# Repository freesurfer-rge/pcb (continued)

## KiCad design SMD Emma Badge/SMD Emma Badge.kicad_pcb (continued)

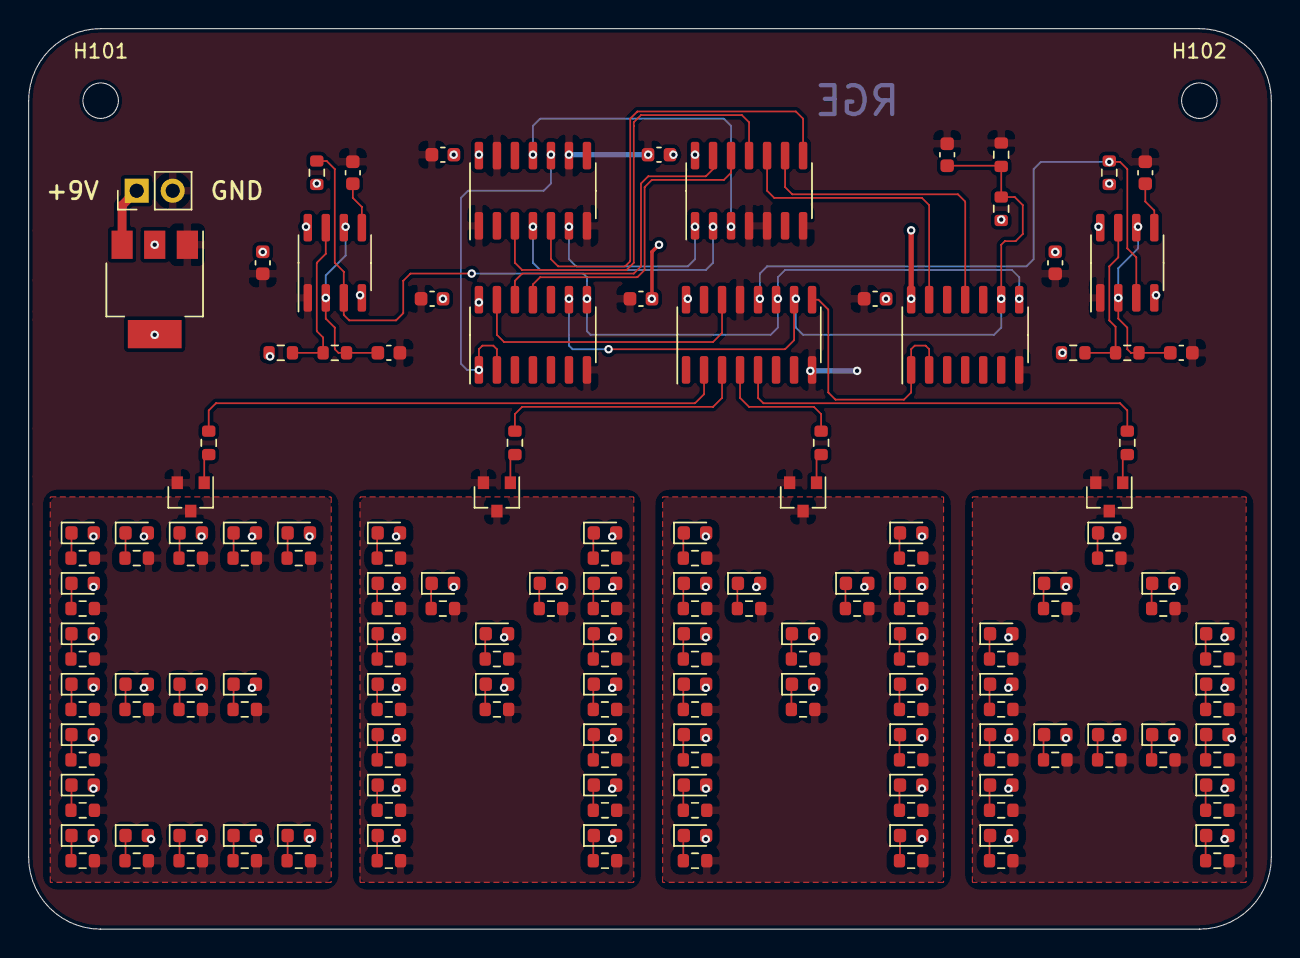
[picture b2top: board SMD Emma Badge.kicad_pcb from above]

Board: 2 copper layers, 87.6 x 63.5 mm, 179 parts (0 on the bottom side), 106 nets.

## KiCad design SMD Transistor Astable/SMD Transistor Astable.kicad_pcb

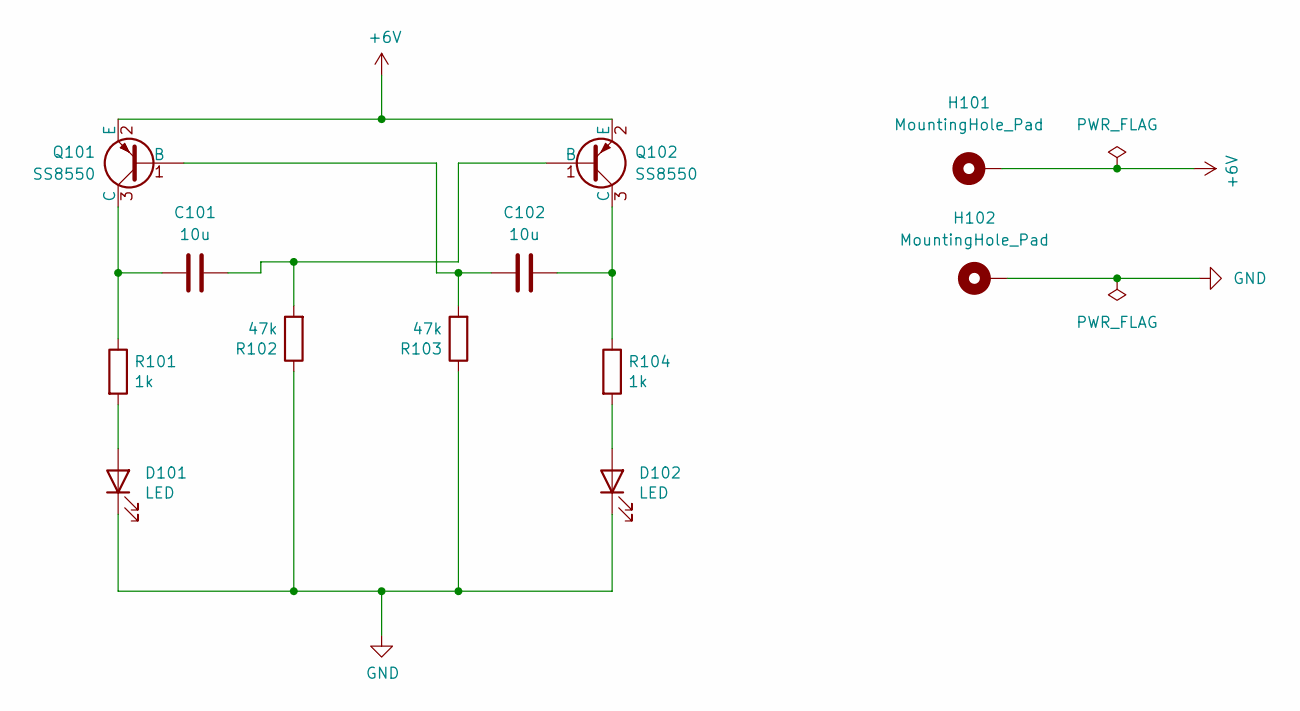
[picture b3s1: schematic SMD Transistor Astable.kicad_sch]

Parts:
C101, C102: 10u; C_0603_1608Metric; LCSC C19702
D101, D102: LED; LED_0603_1608Metric; LCSC C72043
H101, H102: MountingHole_Pad; TestPoint_Pad_2.0x2.0mm
Q101, Q102: SS8550; SOT-23; LCSC C8542
R101, R104: 1k; R_0603_1608Metric; LCSC C21190
R102, R103: 47k; R_0603_1608Metric; LCSC C25819

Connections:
+6V: H101.1, Q101.2 (E), Q102.2 (E)
GND: D101.1 (K), D102.1 (K), H102.1, R102.1, R103.1
unnamed: C101.1, Q101.3 (C), R101.1
unnamed: C101.2, Q102.1 (B), R102.2
unnamed: C102.1, Q101.1 (B), R103.2
unnamed: C102.2, Q102.3 (C), R104.1
unnamed: D101.2 (A), R101.2
unnamed: D102.2 (A), R104.2

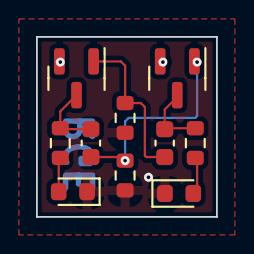
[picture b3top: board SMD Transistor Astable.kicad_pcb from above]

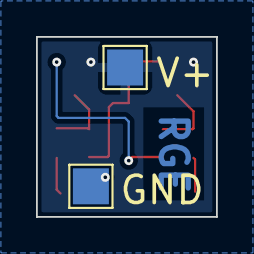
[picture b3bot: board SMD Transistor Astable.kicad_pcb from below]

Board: 2 copper layers, 10.0 x 10.0 mm, 12 parts (2 on the bottom side), 8 nets.

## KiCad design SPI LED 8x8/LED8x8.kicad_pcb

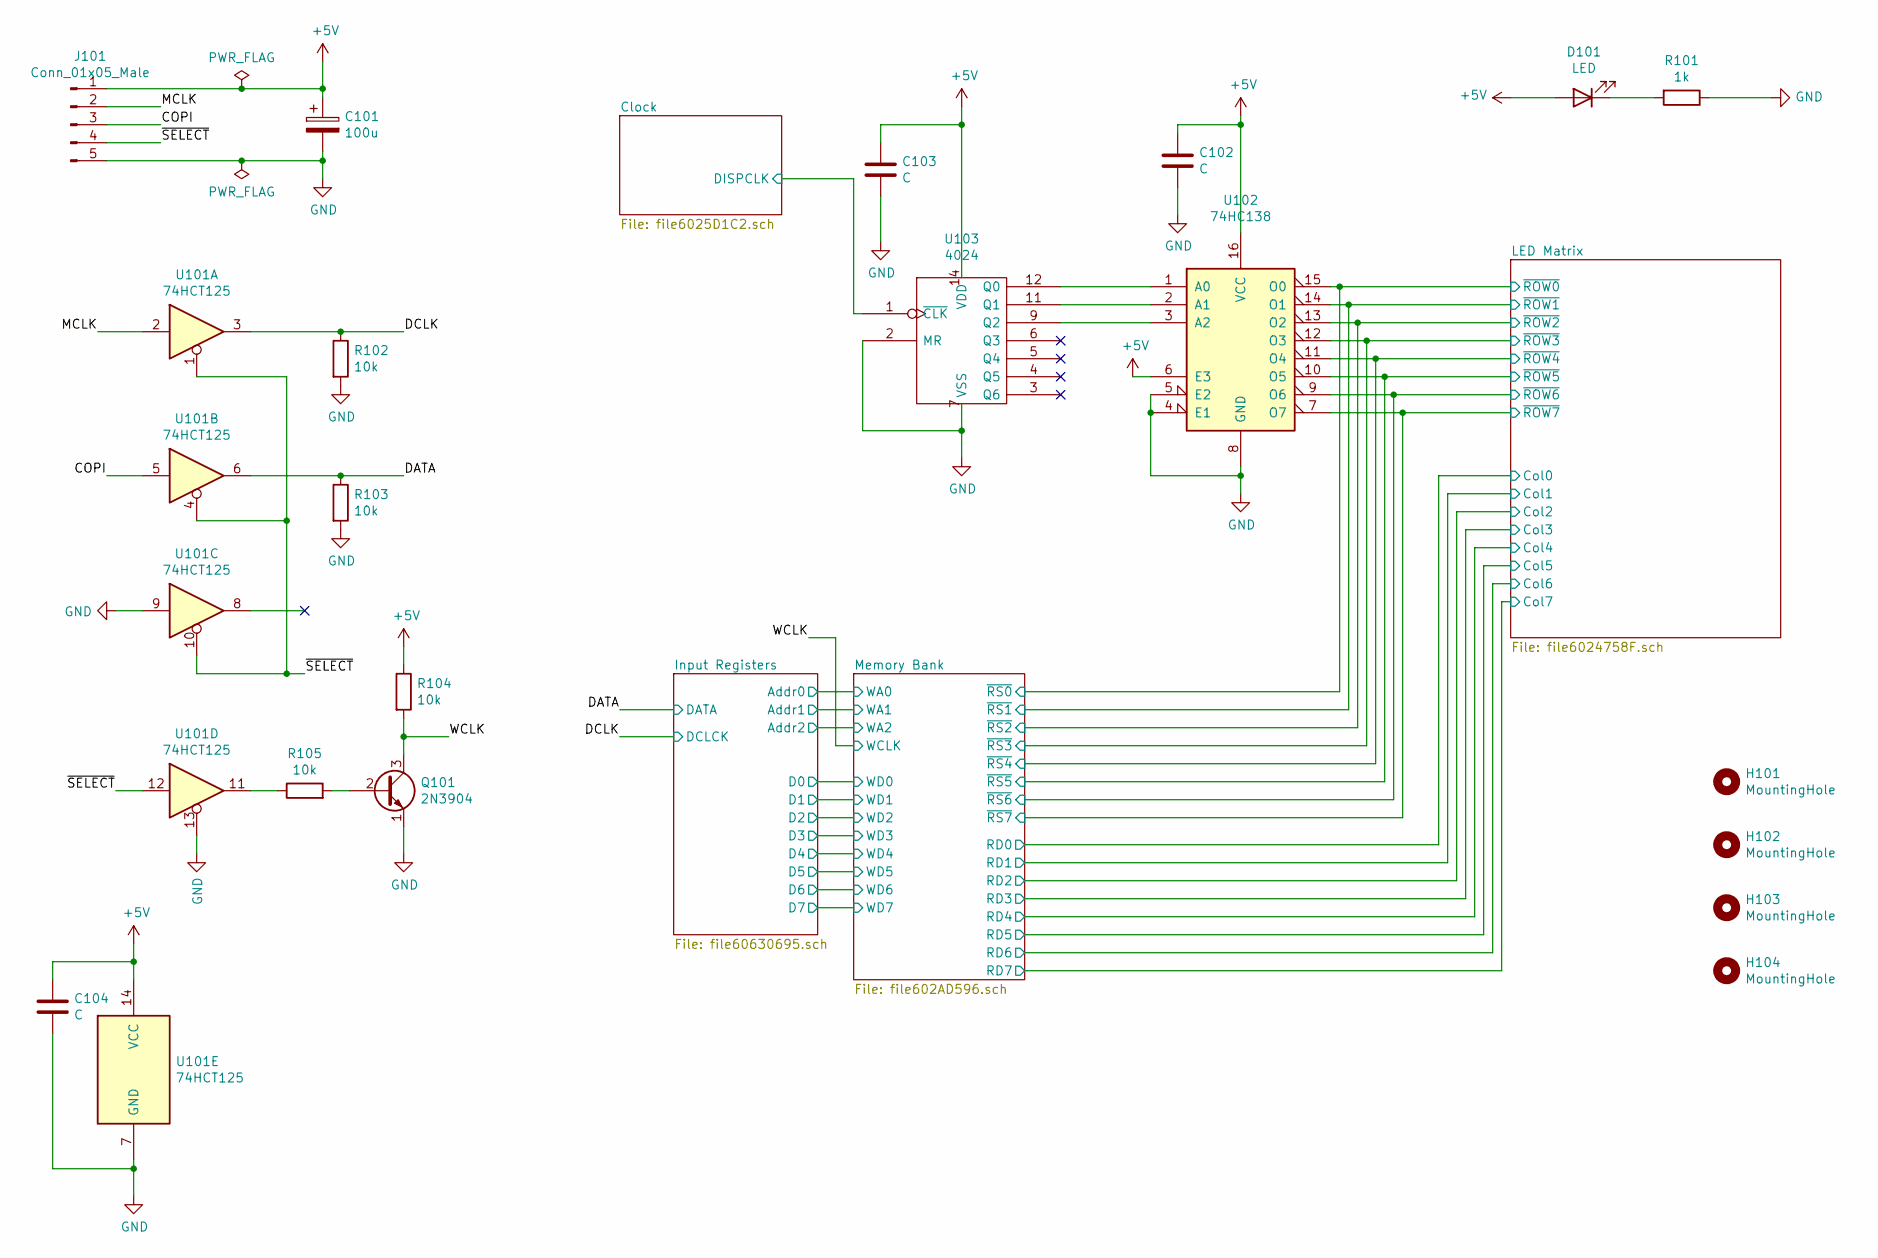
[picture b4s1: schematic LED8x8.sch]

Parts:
C101: 100u; CP_Radial_D5.0mm_P2.50mm
C102: C; C_Disc_D4.3mm_W1.9mm_P5.00mm
C103, C104: C; C_Disc_D4.7mm_W2.5mm_P5.00mm
D101: LED; LED_D5.0mm
H101, H102, H103, H104: MountingHole; MountingHole_2.7mm_M2.5
J101: Conn_01x05_Male; PinHeader_1x05_P2.54mm_Vertical
Q101: 2N3904; TO-92_Wide
R101: 1k; R_Axial_DIN0207_L6.3mm_D2.5mm_P7.62mm_Horizontal
R102, R103, R104, R105: 10k; R_Axial_DIN0207_L6.3mm_D2.5mm_P7.62mm_Horizontal
U101: 74HCT125; DIP-14_W7.62mm_Socket
U102: 74HC138; DIP-16_W7.62mm_Socket
U103: 4024; DIP-14_W7.62mm_Socket

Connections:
+5V: C101.1, C102.2, C103.2, C104.2, D101.2 (A), J101.1, R104.1, U101.14 (VCC), U102.6 (E3), U102.16 (VCC), U103.14 (VDD); also elsewhere on the board
/COPI: J101.3, U101.5
/Clock/DISPCLK: U103.1 (~CLK); also elsewhere on the board
/DATA: R103.1, U101.6; also elsewhere on the board
/DCLK: R102.1, U101.3; also elsewhere on the board
/LED Matrix/~ROW0: U102.15 (O0); also elsewhere on the board
/LED Matrix/~ROW1: U102.14 (O1); also elsewhere on the board
/LED Matrix/~ROW2: U102.13 (O2); also elsewhere on the board
/LED Matrix/~ROW3: U102.12 (O3); also elsewhere on the board
/LED Matrix/~ROW4: U102.11 (O4); also elsewhere on the board
/LED Matrix/~ROW5: U102.10 (O5); also elsewhere on the board
/LED Matrix/~ROW6: U102.9 (O6); also elsewhere on the board
/LED Matrix/~ROW7: U102.7 (O7); also elsewhere on the board
/MCLK: J101.2, U101.2
/WCLK: Q101.3 (C), R104.2; also elsewhere on the board
/~SELECT: J101.4, U101.1, U101.4, U101.10, U101.12
GND: C101.2, C102.1, C103.1, C104.1, J101.5, Q101.1 (E), R101.1, R102.2, R103.2, U101.7 (GND), U101.9, U101.13, U102.4 (E1), U102.5 (E2), U102.8 (GND), U103.2 (MR), U103.7 (VSS); also elsewhere on the board
unnamed: D101.1 (K), R101.2
unnamed: Q101.2 (B), R105.2
unnamed: R105.1, U101.11
unnamed: U102.1 (A0), U103.12 (Q0)
unnamed: U102.2 (A1), U103.11 (Q1)
unnamed: U102.3 (A2), U103.9 (Q2)

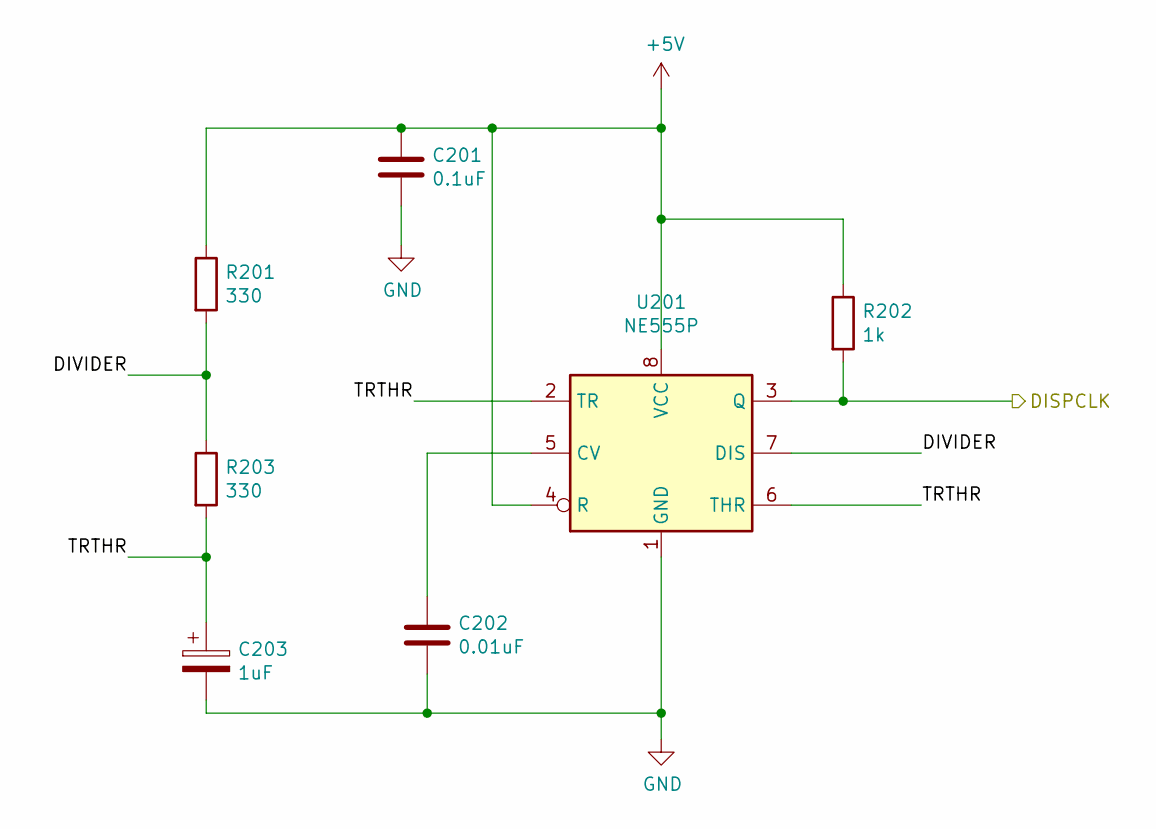
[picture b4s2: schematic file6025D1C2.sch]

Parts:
C201: 0.1uF; C_Disc_D4.3mm_W1.9mm_P5.00mm
C202: 0.01uF; C_Disc_D3.8mm_W2.6mm_P2.50mm
C203: 1uF; CP_Radial_D4.0mm_P1.50mm
R201, R203: 330; R_Axial_DIN0207_L6.3mm_D2.5mm_P7.62mm_Horizontal
R202: 1k; R_Axial_DIN0207_L6.3mm_D2.5mm_P7.62mm_Horizontal
U201: NE555P; DIP-8_W7.62mm_Socket

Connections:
+5V: C201.2, R201.1, R202.1, U201.4 (R), U201.8 (VCC); also elsewhere on the board
/Clock/DISPCLK: R202.2, U201.3 (Q); also elsewhere on the board
/Clock/DIVIDER: R201.2, R203.1, U201.7 (DIS)
/Clock/TRTHR: C203.1, R203.2, U201.2 (TR), U201.6 (THR)
GND: C201.1, C202.2, C203.2, U201.1 (GND); also elsewhere on the board
unnamed: C202.1, U201.5 (CV)

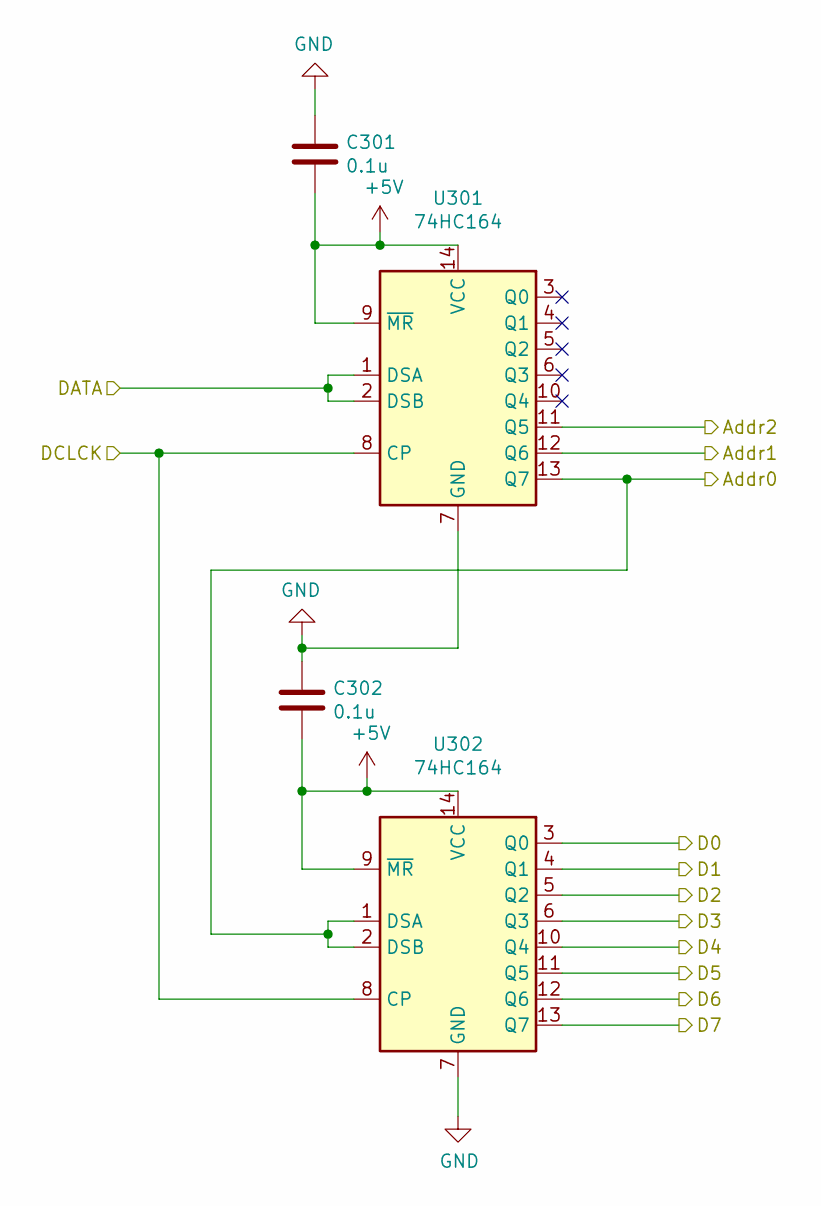
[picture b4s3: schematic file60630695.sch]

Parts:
C301, C302: 0.1u; C_Disc_D4.3mm_W1.9mm_P5.00mm
U301, U302: 74HC164; DIP-14_W7.62mm_Socket

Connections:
+5V: C301.2, C302.2, U301.9 (~MR), U301.14 (VCC), U302.9 (~MR), U302.14 (VCC); also elsewhere on the board
/DATA: U301.1 (DSA), U301.2 (DSB); also elsewhere on the board
/DCLK: U301.8 (CP), U302.8 (CP); also elsewhere on the board
/Input Registers/Addr0: U301.13 (Q7), U302.1 (DSA), U302.2 (DSB); also elsewhere on the board
/Input Registers/Addr1: U301.12 (Q6); also elsewhere on the board
/Input Registers/Addr2: U301.11 (Q5); also elsewhere on the board
/Input Registers/D0: U302.3 (Q0); also elsewhere on the board
/Input Registers/D1: U302.4 (Q1); also elsewhere on the board
/Input Registers/D2: U302.5 (Q2); also elsewhere on the board
/Input Registers/D3: U302.6 (Q3); also elsewhere on the board
/Input Registers/D4: U302.10 (Q4); also elsewhere on the board
/Input Registers/D5: U302.11 (Q5); also elsewhere on the board
/Input Registers/D6: U302.12 (Q6); also elsewhere on the board
/Input Registers/D7: U302.13 (Q7); also elsewhere on the board
GND: C301.1, C302.1, U301.7 (GND), U302.7 (GND); also elsewhere on the board

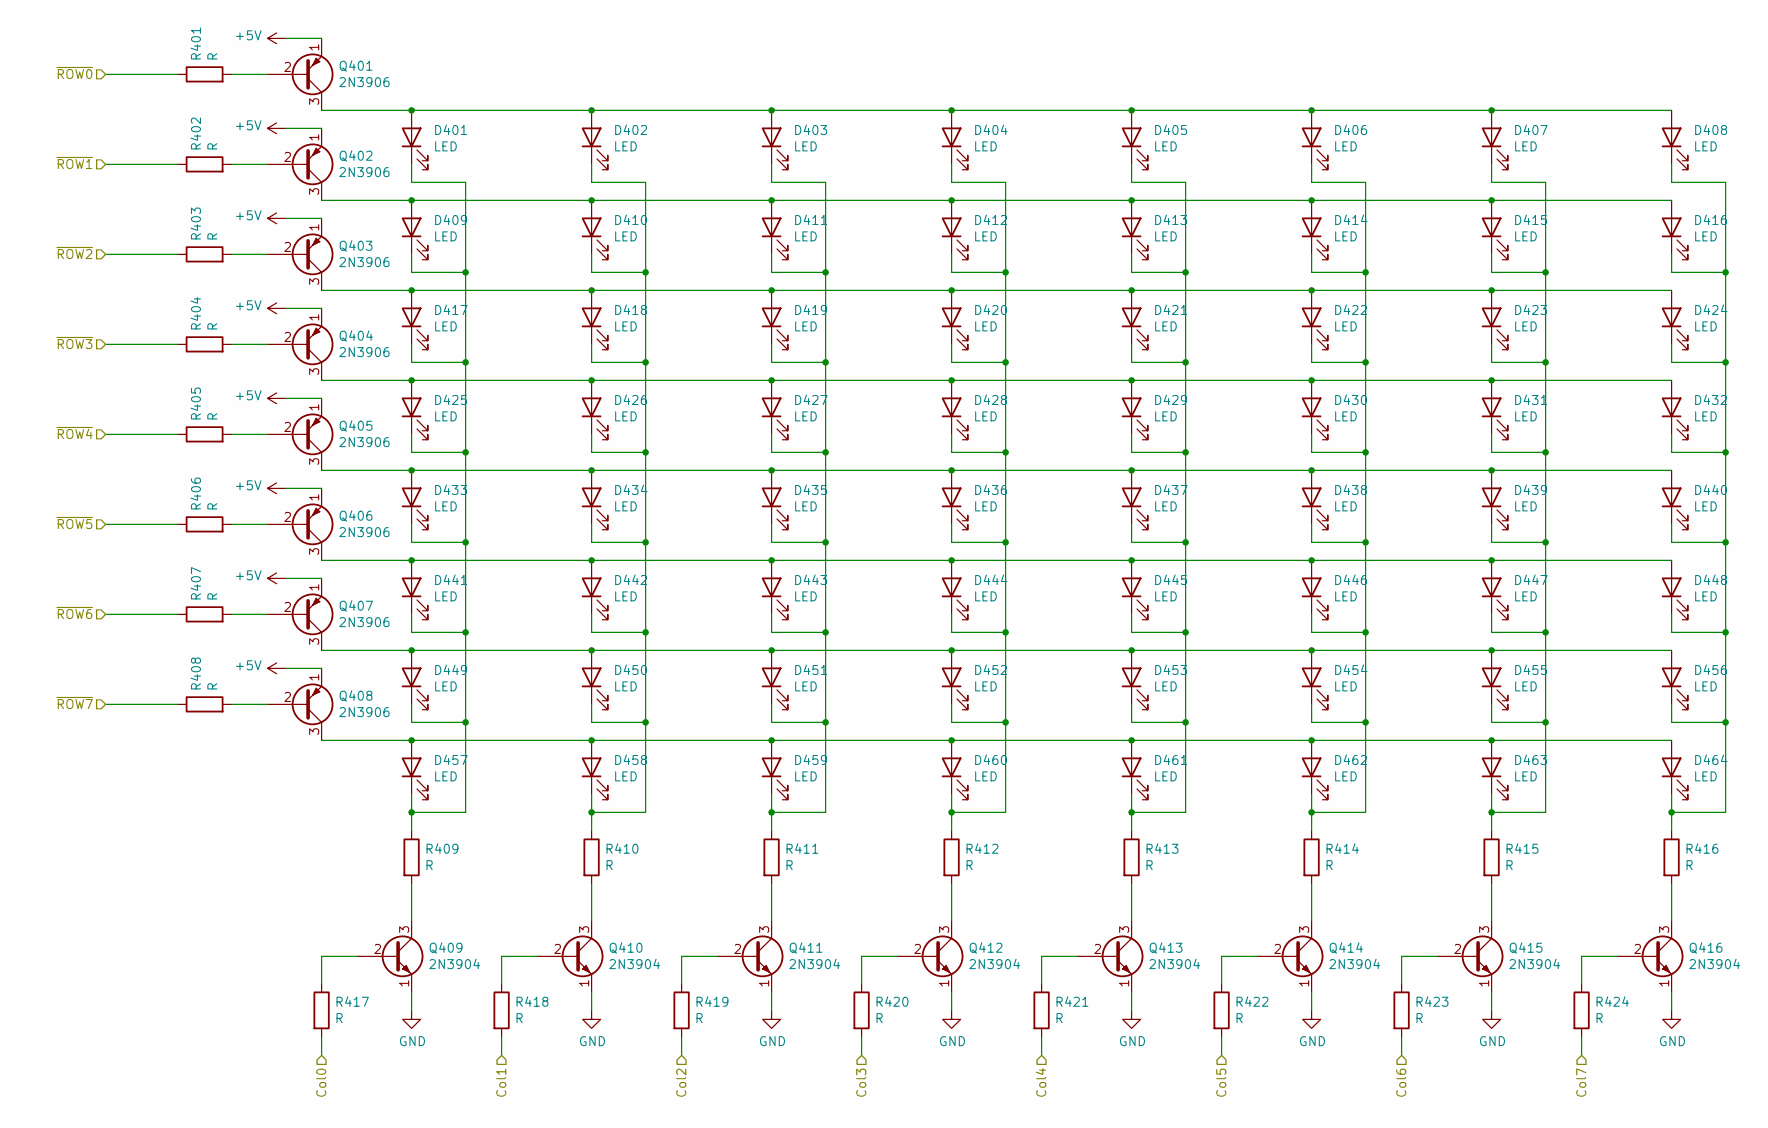
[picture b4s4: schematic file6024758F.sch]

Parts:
D401, D402, D403, D404, D405, D406, D407, D408, D409, D410, D411, D412, D413, D414, D415, D416, D417, D418, D419, D420, D421, D422, D423, D424, D425, D426, D427, D428, D429, D430, D431, D432, D433, D434, D435, D436, D437, D438, D439, D440, D441, D442, D443, D444, D445, D446, D447, D448, D449, D450, D451, D452, D453, D454, D455, D456, D457, D458, D459, D460, D461, D462, D463, D464: LED; LED_D5.0mm
Q401, Q402, Q403, Q404, Q405, Q406, Q407, Q408: 2N3906; TO-92_Wide
Q409, Q410, Q411, Q412, Q413, Q414, Q415, Q416: 2N3904; TO-92_Wide
R401, R402, R403, R404, R405, R406, R407, R408, R409, R410, R411, R412, R413, R414, R415, R416, R417, R418, R419, R420, R421, R422, R423, R424: R; R_Axial_DIN0207_L6.3mm_D2.5mm_P7.62mm_Horizontal

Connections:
+5V: Q401.1 (E), Q402.1 (E), Q403.1 (E), Q404.1 (E), Q405.1 (E), Q406.1 (E), Q407.1 (E), Q408.1 (E); also elsewhere on the board
/LED Matrix/Col0: R417.2; also elsewhere on the board
/LED Matrix/Col1: R418.2; also elsewhere on the board
/LED Matrix/Col2: R419.2; also elsewhere on the board
/LED Matrix/Col3: R420.2; also elsewhere on the board
/LED Matrix/Col4: R421.2; also elsewhere on the board
/LED Matrix/Col5: R422.2; also elsewhere on the board
/LED Matrix/Col6: R423.2; also elsewhere on the board
/LED Matrix/Col7: R424.2; also elsewhere on the board
/LED Matrix/~ROW0: R401.1; also elsewhere on the board
/LED Matrix/~ROW1: R402.1; also elsewhere on the board
/LED Matrix/~ROW2: R403.1; also elsewhere on the board
/LED Matrix/~ROW3: R404.1; also elsewhere on the board
/LED Matrix/~ROW4: R405.1; also elsewhere on the board
/LED Matrix/~ROW5: R406.1; also elsewhere on the board
/LED Matrix/~ROW6: R407.1; also elsewhere on the board
/LED Matrix/~ROW7: R408.1; also elsewhere on the board
GND: Q409.1 (E), Q410.1 (E), Q411.1 (E), Q412.1 (E), Q413.1 (E), Q414.1 (E), Q415.1 (E), Q416.1 (E); also elsewhere on the board
unnamed: D401.1 (K), D409.1 (K), D417.1 (K), D425.1 (K), D433.1 (K), D441.1 (K), D449.1 (K), D457.1 (K), R409.1
unnamed: D401.2 (A), D402.2 (A), D403.2 (A), D404.2 (A), D405.2 (A), D406.2 (A), D407.2 (A), D408.2 (A), Q401.3 (C)
unnamed: D402.1 (K), D410.1 (K), D418.1 (K), D426.1 (K), D434.1 (K), D442.1 (K), D450.1 (K), D458.1 (K), R410.1
unnamed: D403.1 (K), D411.1 (K), D419.1 (K), D427.1 (K), D435.1 (K), D443.1 (K), D451.1 (K), D459.1 (K), R411.1
unnamed: D404.1 (K), D412.1 (K), D420.1 (K), D428.1 (K), D436.1 (K), D444.1 (K), D452.1 (K), D460.1 (K), R412.1
unnamed: D405.1 (K), D413.1 (K), D421.1 (K), D429.1 (K), D437.1 (K), D445.1 (K), D453.1 (K), D461.1 (K), R413.1
unnamed: D406.1 (K), D414.1 (K), D422.1 (K), D430.1 (K), D438.1 (K), D446.1 (K), D454.1 (K), D462.1 (K), R414.1
unnamed: D407.1 (K), D415.1 (K), D423.1 (K), D431.1 (K), D439.1 (K), D447.1 (K), D455.1 (K), D463.1 (K), R415.1
unnamed: D408.1 (K), D416.1 (K), D424.1 (K), D432.1 (K), D440.1 (K), D448.1 (K), D456.1 (K), D464.1 (K), R416.1
unnamed: D409.2 (A), D410.2 (A), D411.2 (A), D412.2 (A), D413.2 (A), D414.2 (A), D415.2 (A), D416.2 (A), Q402.3 (C)
unnamed: D417.2 (A), D418.2 (A), D419.2 (A), D420.2 (A), D421.2 (A), D422.2 (A), D423.2 (A), D424.2 (A), Q403.3 (C)
unnamed: D425.2 (A), D426.2 (A), D427.2 (A), D428.2 (A), D429.2 (A), D430.2 (A), D431.2 (A), D432.2 (A), Q404.3 (C)
unnamed: D433.2 (A), D434.2 (A), D435.2 (A), D436.2 (A), D437.2 (A), D438.2 (A), D439.2 (A), D440.2 (A), Q405.3 (C)
unnamed: D441.2 (A), D442.2 (A), D443.2 (A), D444.2 (A), D445.2 (A), D446.2 (A), D447.2 (A), D448.2 (A), Q406.3 (C)
unnamed: D449.2 (A), D450.2 (A), D451.2 (A), D452.2 (A), D453.2 (A), D454.2 (A), D455.2 (A), D456.2 (A), Q407.3 (C)
unnamed: D457.2 (A), D458.2 (A), D459.2 (A), D460.2 (A), D461.2 (A), D462.2 (A), D463.2 (A), D464.2 (A), Q408.3 (C)
unnamed: Q401.2 (B), R401.2
unnamed: Q402.2 (B), R402.2
unnamed: Q403.2 (B), R403.2
unnamed: Q404.2 (B), R404.2
unnamed: Q405.2 (B), R405.2
unnamed: Q406.2 (B), R406.2
unnamed: Q407.2 (B), R407.2
unnamed: Q408.2 (B), R408.2
unnamed: Q409.2 (B), R417.1
unnamed: Q409.3 (C), R409.2
unnamed: Q410.2 (B), R418.1
unnamed: Q410.3 (C), R410.2
unnamed: Q411.2 (B), R419.1
unnamed: Q411.3 (C), R411.2
unnamed: Q412.2 (B), R420.1
unnamed: Q412.3 (C), R412.2
unnamed: Q413.2 (B), R421.1
unnamed: Q413.3 (C), R413.2
unnamed: Q414.2 (B), R422.1
unnamed: Q414.3 (C), R414.2
unnamed: Q415.2 (B), R423.1
unnamed: Q415.3 (C), R415.2
unnamed: Q416.2 (B), R424.1
unnamed: Q416.3 (C), R416.2

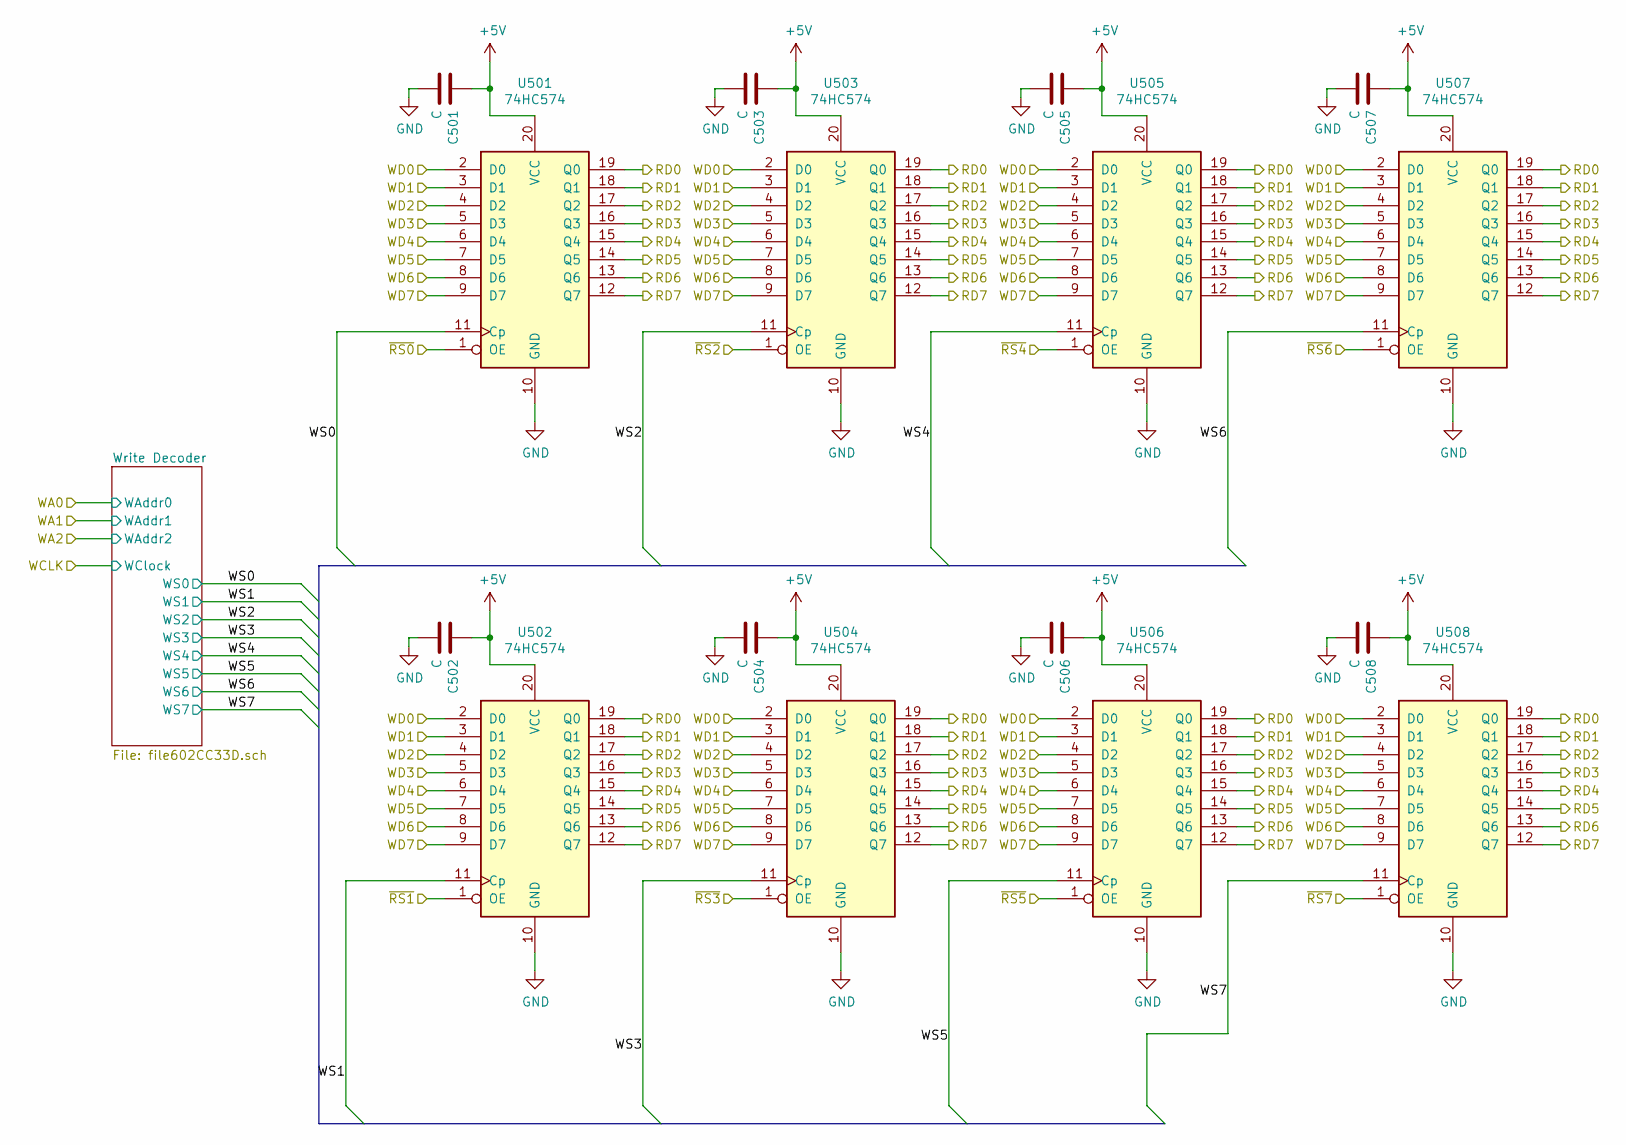
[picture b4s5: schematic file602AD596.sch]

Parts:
C501, C502, C503, C504, C505, C506, C507, C508: C; C_Disc_D4.3mm_W1.9mm_P5.00mm
U501, U502, U503, U504, U505, U506, U507, U508: 74HC574; DIP-20_W7.62mm_Socket

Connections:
+5V: C501.2, C502.2, C503.2, C504.2, C505.2, C506.2, C507.2, C508.2, U501.20 (VCC), U502.20 (VCC), U503.20 (VCC), U504.20 (VCC), U505.20 (VCC), U506.20 (VCC), U507.20 (VCC), U508.20 (VCC); also elsewhere on the board
/Input Registers/D0: U501.2 (D0), U502.2 (D0), U503.2 (D0), U504.2 (D0), U505.2 (D0), U506.2 (D0), U507.2 (D0), U508.2 (D0); also elsewhere on the board
/Input Registers/D1: U501.3 (D1), U502.3 (D1), U503.3 (D1), U504.3 (D1), U505.3 (D1), U506.3 (D1), U507.3 (D1), U508.3 (D1); also elsewhere on the board
/Input Registers/D2: U501.4 (D2), U502.4 (D2), U503.4 (D2), U504.4 (D2), U505.4 (D2), U506.4 (D2), U507.4 (D2), U508.4 (D2); also elsewhere on the board
/Input Registers/D3: U501.5 (D3), U502.5 (D3), U503.5 (D3), U504.5 (D3), U505.5 (D3), U506.5 (D3), U507.5 (D3), U508.5 (D3); also elsewhere on the board
/Input Registers/D4: U501.6 (D4), U502.6 (D4), U503.6 (D4), U504.6 (D4), U505.6 (D4), U506.6 (D4), U507.6 (D4), U508.6 (D4); also elsewhere on the board
/Input Registers/D5: U501.7 (D5), U502.7 (D5), U503.7 (D5), U504.7 (D5), U505.7 (D5), U506.7 (D5), U507.7 (D5), U508.7 (D5); also elsewhere on the board
/Input Registers/D6: U501.8 (D6), U502.8 (D6), U503.8 (D6), U504.8 (D6), U505.8 (D6), U506.8 (D6), U507.8 (D6), U508.8 (D6); also elsewhere on the board
/Input Registers/D7: U501.9 (D7), U502.9 (D7), U503.9 (D7), U504.9 (D7), U505.9 (D7), U506.9 (D7), U507.9 (D7), U508.9 (D7); also elsewhere on the board
/LED Matrix/Col0: U501.19 (Q0), U502.19 (Q0), U503.19 (Q0), U504.19 (Q0), U505.19 (Q0), U506.19 (Q0), U507.19 (Q0), U508.19 (Q0); also elsewhere on the board
/LED Matrix/Col1: U501.18 (Q1), U502.18 (Q1), U503.18 (Q1), U504.18 (Q1), U505.18 (Q1), U506.18 (Q1), U507.18 (Q1), U508.18 (Q1); also elsewhere on the board
/LED Matrix/Col2: U501.17 (Q2), U502.17 (Q2), U503.17 (Q2), U504.17 (Q2), U505.17 (Q2), U506.17 (Q2), U507.17 (Q2), U508.17 (Q2); also elsewhere on the board
/LED Matrix/Col3: U501.16 (Q3), U502.16 (Q3), U503.16 (Q3), U504.16 (Q3), U505.16 (Q3), U506.16 (Q3), U507.16 (Q3), U508.16 (Q3); also elsewhere on the board
/LED Matrix/Col4: U501.15 (Q4), U502.15 (Q4), U503.15 (Q4), U504.15 (Q4), U505.15 (Q4), U506.15 (Q4), U507.15 (Q4), U508.15 (Q4); also elsewhere on the board
/LED Matrix/Col5: U501.14 (Q5), U502.14 (Q5), U503.14 (Q5), U504.14 (Q5), U505.14 (Q5), U506.14 (Q5), U507.14 (Q5), U508.14 (Q5); also elsewhere on the board
/LED Matrix/Col6: U501.13 (Q6), U502.13 (Q6), U503.13 (Q6), U504.13 (Q6), U505.13 (Q6), U506.13 (Q6), U507.13 (Q6), U508.13 (Q6); also elsewhere on the board
/LED Matrix/Col7: U501.12 (Q7), U502.12 (Q7), U503.12 (Q7), U504.12 (Q7), U505.12 (Q7), U506.12 (Q7), U507.12 (Q7), U508.12 (Q7); also elsewhere on the board
/LED Matrix/~ROW0: U501.1 (OE); also elsewhere on the board
/LED Matrix/~ROW1: U502.1 (OE); also elsewhere on the board
/LED Matrix/~ROW2: U503.1 (OE); also elsewhere on the board
/LED Matrix/~ROW3: U504.1 (OE); also elsewhere on the board
/LED Matrix/~ROW4: U505.1 (OE); also elsewhere on the board
/LED Matrix/~ROW5: U506.1 (OE); also elsewhere on the board
/LED Matrix/~ROW6: U507.1 (OE); also elsewhere on the board
/LED Matrix/~ROW7: U508.1 (OE); also elsewhere on the board
/Memory Bank/WS0: U501.11 (Cp); also elsewhere on the board
/Memory Bank/WS1: U502.11 (Cp); also elsewhere on the board
/Memory Bank/WS2: U503.11 (Cp); also elsewhere on the board
/Memory Bank/WS3: U504.11 (Cp); also elsewhere on the board
/Memory Bank/WS4: U505.11 (Cp); also elsewhere on the board
/Memory Bank/WS5: U506.11 (Cp); also elsewhere on the board
/Memory Bank/WS6: U507.11 (Cp); also elsewhere on the board
/Memory Bank/WS7: U508.11 (Cp); also elsewhere on the board
GND: C501.1, C502.1, C503.1, C504.1, C505.1, C506.1, C507.1, C508.1, U501.10 (GND), U502.10 (GND), U503.10 (GND), U504.10 (GND), U505.10 (GND), U506.10 (GND), U507.10 (GND), U508.10 (GND); also elsewhere on the board

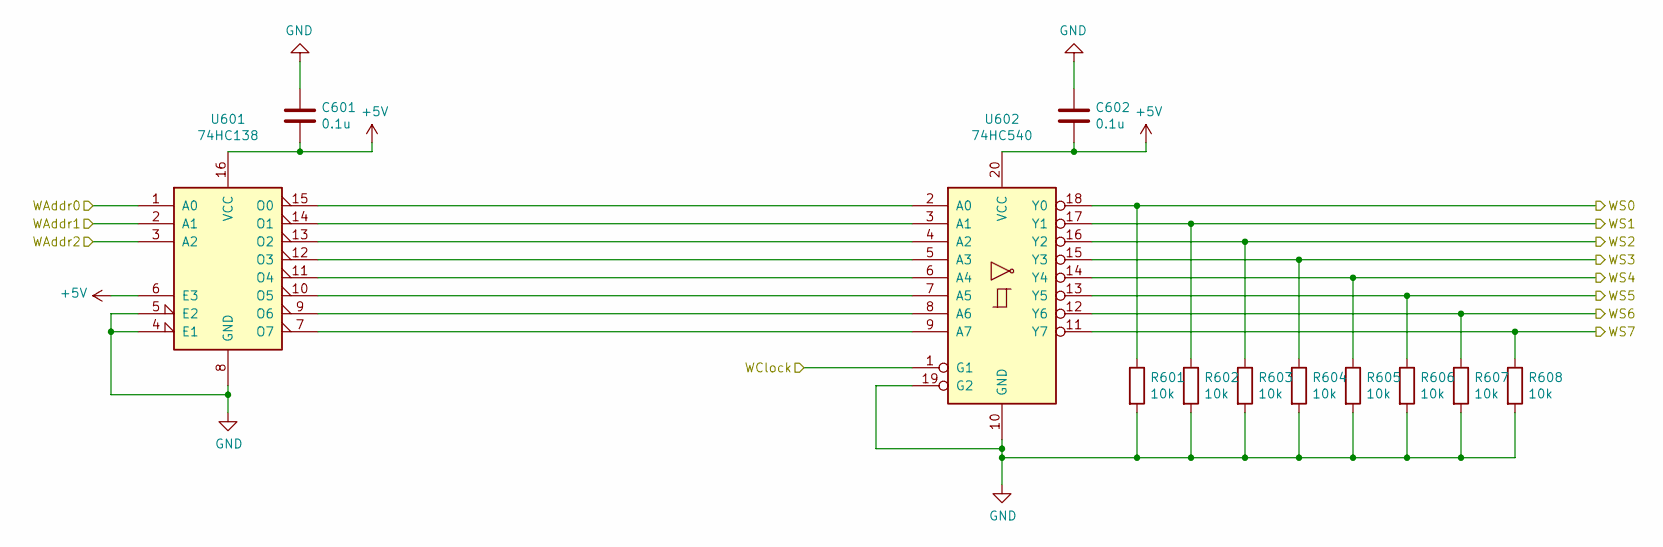
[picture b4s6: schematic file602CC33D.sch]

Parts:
C601, C602: 0.1u; C_Disc_D4.3mm_W1.9mm_P5.00mm
R601, R602, R603, R604, R605, R606, R607, R608: 10k; R_Axial_DIN0207_L6.3mm_D2.5mm_P7.62mm_Horizontal
U601: 74HC138; DIP-16_W7.62mm_Socket
U602: 74HC540; DIP-20_W7.62mm_Socket

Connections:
+5V: C601.2, C602.2, U601.6 (E3), U601.16 (VCC), U602.20 (VCC); also elsewhere on the board
/Input Registers/Addr0: U601.1 (A0); also elsewhere on the board
/Input Registers/Addr1: U601.2 (A1); also elsewhere on the board
/Input Registers/Addr2: U601.3 (A2); also elsewhere on the board
/Memory Bank/WS0: R601.1, U602.18 (Y0); also elsewhere on the board
/Memory Bank/WS1: R602.1, U602.17 (Y1); also elsewhere on the board
/Memory Bank/WS2: R603.1, U602.16 (Y2); also elsewhere on the board
/Memory Bank/WS3: R604.1, U602.15 (Y3); also elsewhere on the board
/Memory Bank/WS4: R605.1, U602.14 (Y4); also elsewhere on the board
/Memory Bank/WS5: R606.1, U602.13 (Y5); also elsewhere on the board
/Memory Bank/WS6: R607.1, U602.12 (Y6); also elsewhere on the board
/Memory Bank/WS7: R608.1, U602.11 (Y7); also elsewhere on the board
/WCLK: U602.1 (G1); also elsewhere on the board
GND: C601.1, C602.1, R601.2, R602.2, R603.2, R604.2, R605.2, R606.2, R607.2, R608.2, U601.4 (E1), U601.5 (E2), U601.8 (GND), U602.10 (GND), U602.19 (G2); also elsewhere on the board
unnamed: U601.7 (O7), U602.9 (A7)
unnamed: U601.9 (O6), U602.8 (A6)
unnamed: U601.10 (O5), U602.7 (A5)
unnamed: U601.11 (O4), U602.6 (A4)
unnamed: U601.12 (O3), U602.5 (A3)
unnamed: U601.13 (O2), U602.4 (A2)
unnamed: U601.14 (O1), U602.3 (A1)
unnamed: U601.15 (O0), U602.2 (A0)

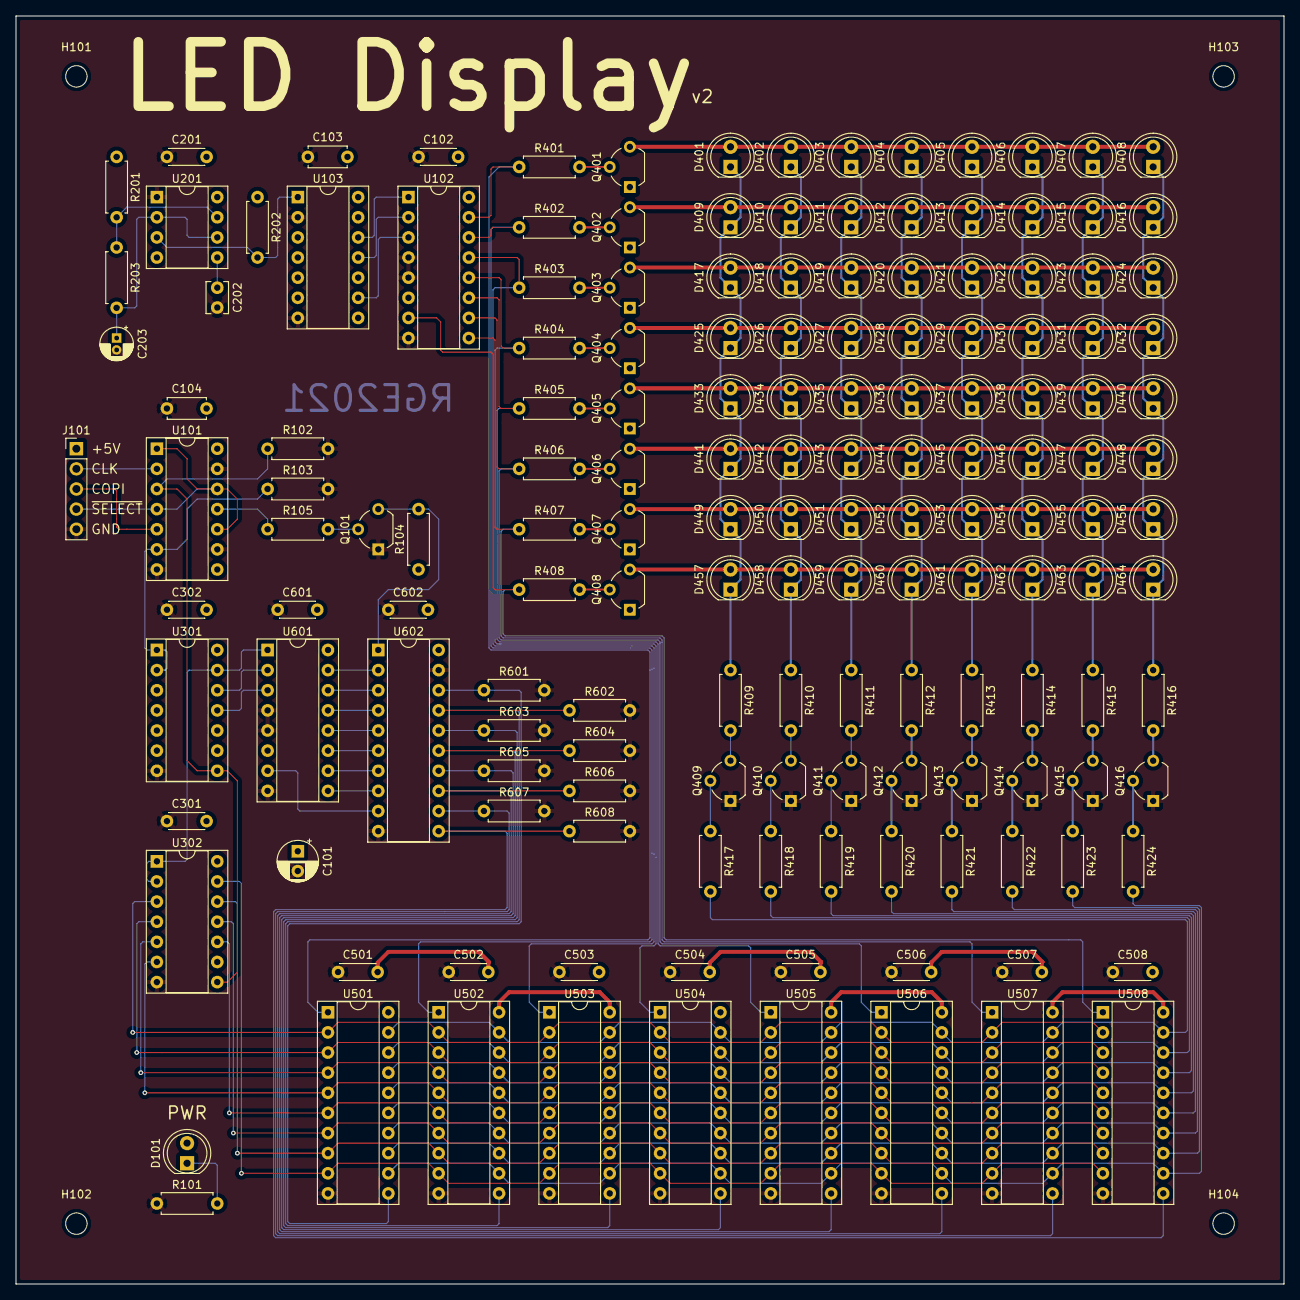
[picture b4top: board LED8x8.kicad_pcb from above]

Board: 2 copper layers, 160.0 x 160.0 mm, 162 parts (0 on the bottom side), 101 nets.
